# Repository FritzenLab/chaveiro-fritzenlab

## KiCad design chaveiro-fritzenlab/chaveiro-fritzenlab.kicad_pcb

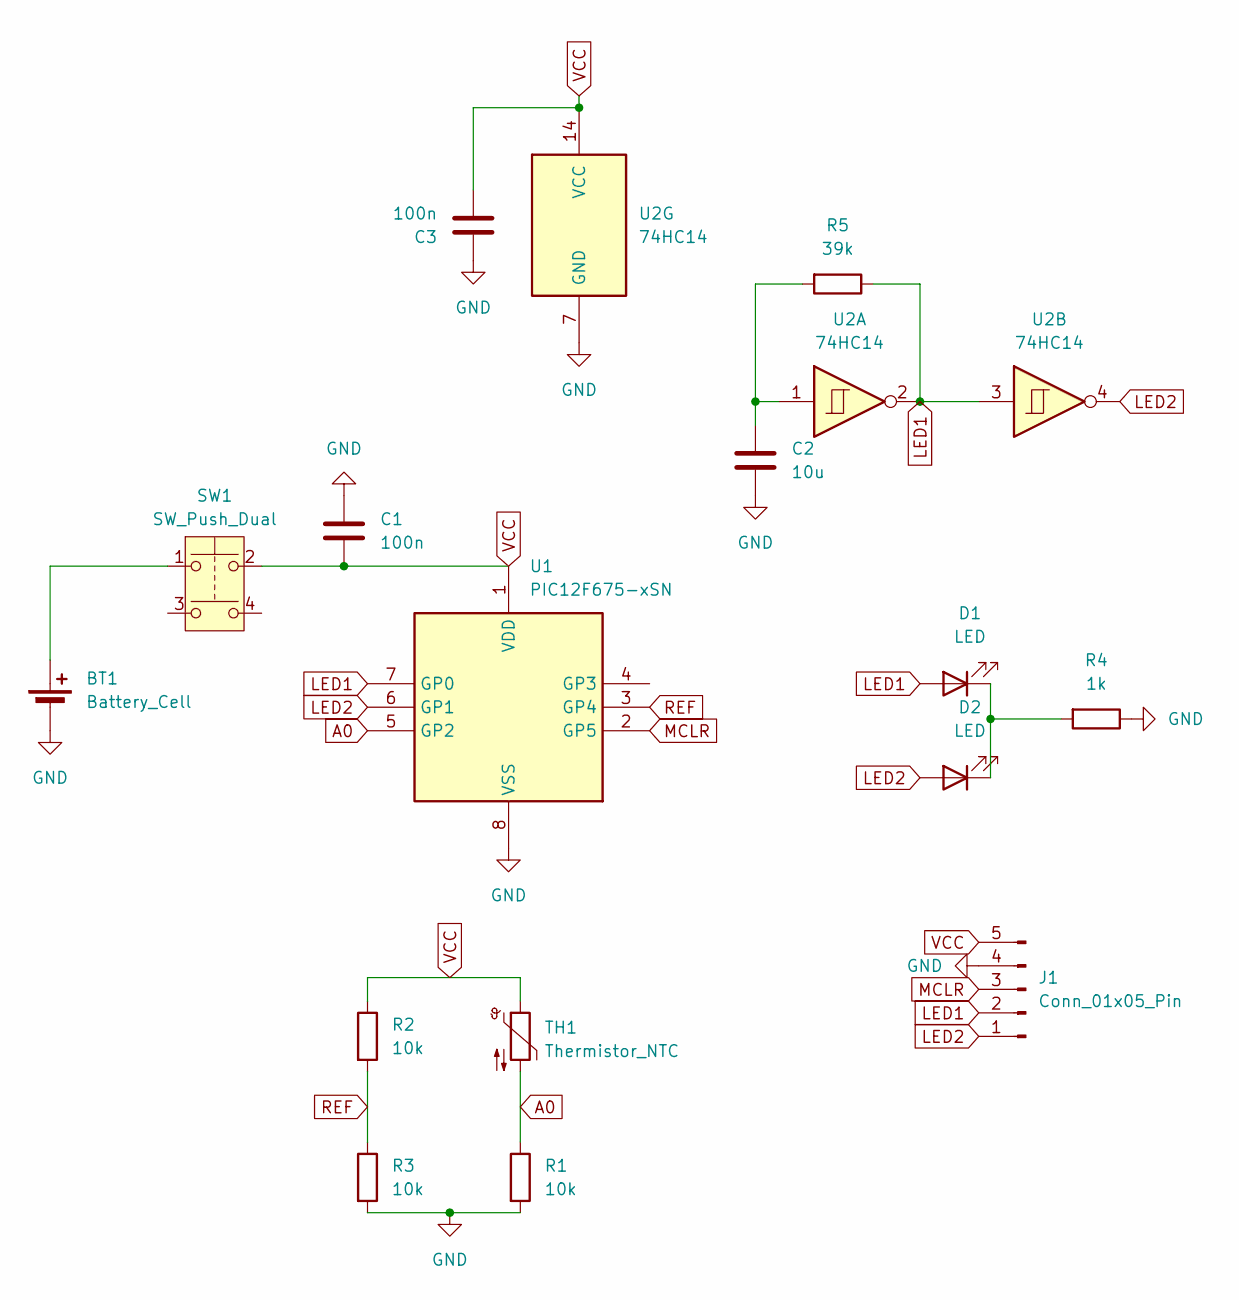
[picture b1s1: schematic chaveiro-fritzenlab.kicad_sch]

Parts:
BT1: Battery_Cell; BatteryHolder_Multicomp_BC-2001_1x2032
C1, C3: 100n; C_0805_2012Metric
C2: 10u; C_1210_3225Metric
D1, D2: LED; LED_0805_2012Metric
J1: Conn_01x05_Pin; PinHeader_1x05_P2.54mm_Vertical
R1, R2, R3: 10k; R_0805_2012Metric
R4: 1k; R_0805_2012Metric
R5: 39k; R_0805_2012Metric
SW1: SW_Push_Dual; SW_Push_1P1T_NO_6x6mm_H9.5mm
TH1: Thermistor_NTC; R_0805_2012Metric
U1: PIC12F675-xSN; SOIC-8_3.9x4.9mm_P1.27mm
U2: 74HC14; SOIC-14_3.9x8.7mm_P1.27mm

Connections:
A0: R1.1, TH1.2, U1.5 (GP2)
GND: BT1.2 (-), C1.2, C2.2, C3.2, J1.4, R1.2, R3.2, R4.1, U1.8 (VSS), U2.7 (GND)
LED1: D1.2 (A), J1.2, R5.1, U1.7 (GP0), U2.2, U2.3
LED2: D2.2 (A), J1.1, U1.6 (GP1), U2.4
MCLR: J1.3, U1.2 (GP5)
unnamed: BT1.1 (+), SW1.1
unnamed: C2.1, R5.2, U2.1
unnamed: D1.1 (K), D2.1 (K), R4.2
REF: R2.2, R3.1, U1.3 (GP4)
VCC: C1.1, C3.1, J1.5, R2.1, SW1.2, TH1.1, U1.1 (VDD), U2.14 (VCC)

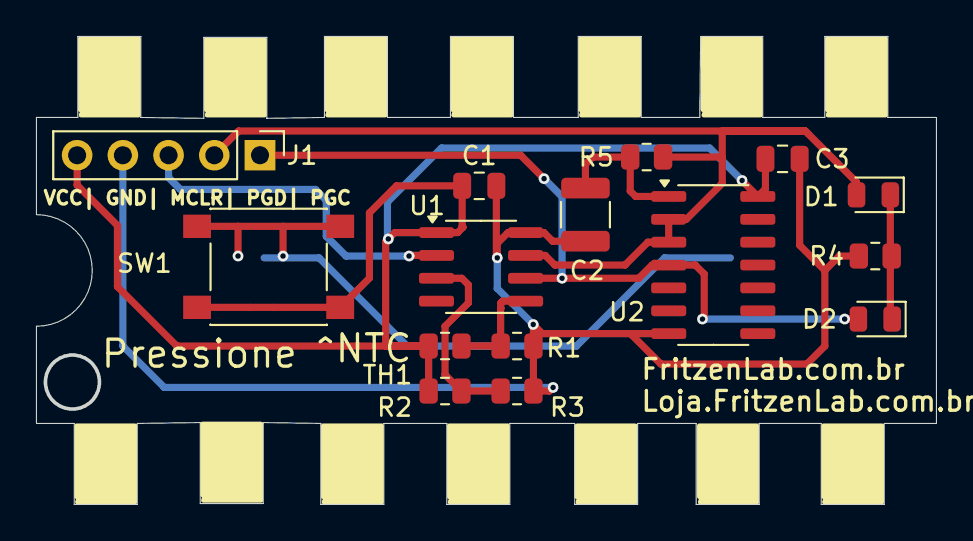
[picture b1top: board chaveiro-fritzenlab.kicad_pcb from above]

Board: 2 copper layers, 49.9 x 25.9 mm, 16 parts (1 on the bottom side), 10 nets.

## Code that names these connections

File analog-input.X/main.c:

/*
 Timer based on this code: https://microcontroladores-c.blogspot.com/2014/09/timer0-com-pic12f675.html
 * AD converter based on: https://forum.microchip.com/s/topic/a5C3l000000MRbeEAG/t336178
 * AD code also from here: https://saeedsolutions.blogspot.com/2012/07/pic12f675-adc-code-proteus-simulation.html
 */
#include <stdio.h>
#include <stdlib.h>
#include <xc.h>
#include <math.h>
#define _XTAL_FREQ 4000000

#define LED1 GP0
#define LED2 GP1
/////////////////////////////////////////////////////////configuraçôes//////////////////////////////////////////////////
#pragma config FOSC = INTRCIO   // Oscillator Selection bits (INTOSC oscillator: I/O function on GP4/OSC2/CLKOUT pin, I/O function on GP5/OSC1/CLKIN)
#pragma config WDTE = OFF       // Watchdog Timer Enable bit (WDT disabled)
#pragma config PWRTE = ON       // Power-Up Timer Enable bit (PWRT enabled)
#pragma config MCLRE = OFF      // GP3/MCLR pin function select (GP3/MCLR pin function is digital I/O, MCLR internally tied to VDD)
#pragma config BOREN = OFF      // Brown-out Detect Enable bit (BOD disabled)
#pragma config CP = OFF         // Code Protection bit (Program Memory code protection is disabled)
#pragma config CPD = OFF         // Data Code Protection bit (Data memory code protection is enabled)


volatile uint8_t counter= 0;
volatile int reading= 0;
volatile unsigned int voltage= 0;
volatile uint8_t readAndDecide= 1;
volatile int tens= 0;
volatile int units= 0;
volatile uint8_t executeTens= 0;
volatile uint8_t executeUnits= 0;
volatile long temp_x100= 0;
void __interrupt() isr()//interrupt vector
{   
    counter++;
    if(counter == 4){
        counter= 0;
        
        if(readAndDecide == 1){
            readAndDecide= 0;
            executeTens= 1;
            executeUnits= 0;
            
            GO_nDONE= 1;        
            while(GO_nDONE);
            /*reading = ((ADRESH<<8)+ADRESL); 
            // Temperature (°C) = -19.784 * V + 75.304
            // V = reading * 5.0 / 1024
            // for 3.3V: Temp = (-32.974 * V) + 75.304
            // do temp_x100 = (-32974L * reading * 33) / 10240 + 7530; // for 3.3V
            // So, Temp = (-19.784 * reading * 5 / 1024) + 75.304
            //temp_x100 = (-19784L * reading * 5) / 1024 + 7530; // for 5V
            temp_x100 = (-9892L * reading) / 1023 + 7530; // for 3.3V
            voltage = temp_x100 / 100;*/
            
            // NTC on top
            reading = ((ADRESH << 8) + ADRESL); // 0?1023
            // Step 1: Vadc in millivolts
            int vadc_mV = (reading * 3300L) / 1023;
            // Step 2: Calculate NTC resistance
            int r_ntc = (10000L * (3300L - vadc_mV)) / vadc_mV;
            // Step 3: Linear temperature approximation (0?50ºC)
            int temp_x100 = ((48400L - r_ntc) * 100) / 903;
            // Optional: Convert to °C
            voltage = (temp_x100 / 100) - 20;
            
                       
            if(voltage >= 40){
                tens= 4;
                units= voltage - 40;
            }else if(voltage >= 30){
                tens= 3;
                units= voltage - 30;
            }else if(voltage >= 20){
                tens= 2;
                units= voltage - 20;
            }else if(voltage >= 10){
                tens= 1;
                units= voltage - 10;
            }else{
                tens= 0;
                units= voltage;
            }
            tens= tens * 2;
            units= units * 2;
        }else if(executeTens == 1){
            tens--;
            LED2= 0;
            if(LED1){
                LED1= 0;
            }else{
                LED1= 1;
            }
            if(tens < 1){
                executeTens= 0;
                executeUnits= 1;
            }
            
        }else if(executeUnits == 1){
            LED1= 0;
            units--;
            if(LED2){
                LED2= 0;
            }else{
                LED2= 1;
            }
            if(units < 1){
                executeTens= 0;
                executeUnits= 0;
                readAndDecide= 1;
            }
            
        }
        
        
        
        
    }
    
    TMR0IF = 0;//  clear timer0 interrupt flag
    TMR0 = 0;// zeroes timer 0 counting, so that it couts from 256 down to 0 again
}


//////////////////////////////////////////////////////Main routine///////////////////////////////////////////////////////////////
void main(void) {
    TRISIO = 0b010100;// GP2 and GP4 analog inputs
    CMCON = 7;// disable comparators
    ANSEL = 0b00011100;// AN2 and AN3 as analog inputs  
    ADCON0=0b10001001; // AN2, right justified, VDD as ref
    //ADCON0=0b10001101; // AN3, right justified, VDD as ref
    ADON=1; // Enable ADC
    WPU = 0X00;// pull ups disabled
    TMR0 = 0;
    OSCCAL = 0b11111111;// internal oscillator to max frequency
    OPTION_REG = 0b10000111;
    INTCON = 0b11100000;
    
    
    
   
    
    while(1)
    {
        
        
    }//infinite loop

}

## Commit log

2024-11-04 finished design
2024-11-04 backups
2025-01-18 added pic sketch files
2025-01-18 added code for analog input
2025-01-19 edited code
2026-05-03 Claude.ai editou/melhorou o código
    Claude.ai editou/melhorou o código
